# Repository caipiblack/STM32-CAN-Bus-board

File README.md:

STM32-CAN-Bus-board
-------------------

CAN Bus shield with external power supply (12V/24V) for NUCLEO-L432KC board.

All the pins of the NUCLEO-L432KC board are available on the connectors of the shield.

The available pins provide many peripherals (ADC, SPI, I2C, GPIO and more) that can be used for many projects (IOT sensors, security sensors, automation...)

# Hardware

This part describe how the schematic was made, how to mount the PCB and how to test it.

**IMPORTANT: This shield require some modifications on the Nucleo board to works (due to external supply) (see after)**

## Kicad project

The Kicad project as been created with the version 8.0.1 of Kicad.

Most of the symbols and footprints comes from the default libraries.

The custom footprints are stored in the `custom` folder near the Kicad project.

Setup Kicad on Ubuntu 24.04:

```
sudo add-apt-repository ppa:kicad/kicad-8.0-releases
sudo apt update
sudo apt install kicad
```

The last production files are stored in the directory [hardware/rev_a/fab](hardware/rev_a/fab).

## Configuration of the NUCLEO-L432KC board

Some modifications are required to be able to power the Nucleo board from external 3V3 regulator (provided by the shield):
- Remove the jumper!
- Remove SB9.
- Remove SB14.

After these changes:
- The 3V3 power for the STM32 will be provided by "external power source" (the shield).
- The debug/flash side of Nucleo board will not be powered by the "external power source" (the shield).
- To flash or debug the Nucleo board, the Nucleo board must be connected by USB to the computer (The St-Link chip will be powered by 5V>3V regulator in the Nucleo board) AND the 3V3 power must be supplied by the shield (to power the STM32 chip).

## PCB mounting instructions

Mount the components on the board:
1. Take the PCB and fix it to the table.
2. Put solder past on all CMS pads.
3. Configure your hot air machine with something like this:
- Speed: 3/8.
- Temperature: 300°C.
4. Solder the CMS components in this order: D4, D6, D1, D5, D2, U2, U3.
5. Solder the other components in this order: C1, C10, C4, R4, R2, R6, R3, R5, F1, Jumper, C6, C5, L1.
6. Mount the `NUCLEO-L432KC` board in the headers and solder the headers to the PCB (Doing it like this prevent issues with headers that are not perfectly vertical or parallel).
7. Remove the nucleo board from the soldered headers.

## PCB testing instructions

Testing instructions:
- Remove the `NUCLEO-L432KC` board from the headers.
- Power on the board with laboratory power supply configured at 12V with current limited to 50mA.
  - At this point the power consumption (on 12V line) should be less than 10mA.
  - Measure the voltage in the 3V3 pin and check that the voltage is around 3.3V.
- If the previous tests pass, turn off the power and plug the `NUCLEO-L432KC` board in the headers then turn on the power.
  - At this point the power consumption (on 12V line) should be less than 10mA.
- If the previous tests pass, connect the `NUCLEO-L432KC` board to the computer and flash it with the template project.
- Test the CAN interface:
  - Plug a USB<>CAN device from a Linux computer to the board.
  - On the computer, execute these commands:
```
sudo apt-get install can-utils
sudo modprobe vcan
sudo ip link add dev can0 type vcan
sudo ip link set up can0 type can bitrate 250000
candump -td -a can0
```
  - Reset the board
  - On the `candump` you should see something like this:
```
 (000.000000)  can0  71D   [1]  00                        '.'
```

# Software

This repository comes with a demo software in the `software` directory: This software act like a CANopen node and permits to control the LED of the `NUCLEO-L432KC` board.

This guide also describe how to create a project from scratch for the `STM32-CAN-Bus-board` board.

The LED can be controlled by writing in the object at index `0x6001`. (See examples at `CANopenLinux` section).

## Tools setup

1. Download and install `STM32CubeIDE` from [here](https://www.st.com/en/development-tools/stm32cubeide.html)
2. (Optional) Download and install `STM32CubeProg` from [here](https://www.st.com/en/development-tools/stm32cubeprog.html). (This tool can be used to only flash the `NUCLEO-L432KC` board without the IDE)

### Compatibility issues of STM32CubeIDE with Ubuntu 24.04

There are issues with `STM32CubeIDE` on `Ubuntu 24.04` because it has a dependecy to `libncurses5` and this is not available with this version of Ubuntu.

This dependency is required by the `arm-none-eabi-gdb` provided by ST.

To resolve the problem:
- Install the generic linux version of `STM32CubeIDE` instead of the version from `.deb` (as it will not check the dependency).
- Install `arm-none-eabi-gdb` or `gdb-multiarch` and create a link to provide `arm-none-eabi-gdb`:
```
sudo apt install gdb-multiarch
sudo ln -s /usr/bin/gdb-multiarch /usr/bin/arm-none-eabi-gdb
```
- In your project configuration `Project Properties -> C/C++ Build -> Environment -> PATH` add `/usr/bin` at the first place to use `arm-none-eabi-gdb` provided by `/usr/bin` instead of ST directories.

## Create a project from scratch

Base project creation:
1. Open `STM32CubeIDE`.
2. Press `File > New > STM32 Project`.
3. Press `Board Selector`.
4. Search `Commercial Part Number` with `NUCLEO-L432KC`, then select it and press Next
5. Specify the `Project Name` and `Location`, then press `Finish`.
6. Configure the peripheral in defaults state and open the configuration tool (or open `.ioc` file).
7. Change the configuration of `PA0` to `Reset_State` as we don't have MCO clock source when the `NUCLEO-L432KC` is externaly powered from 3V3 (because MCO comes from the St-Link chip and it is not powered in this situation).
8. In `Clock Configuration`:
- Select `System Clock Mux` to use `PLLCLK`
- Select `PLL Source Mux` to `MSI`
- Configure the PLL with `X48` and `/4` to get 48Mhz in SYSCLK and APBs

For the integration of `CANopenNode` stack see the README of [CanOpenSTM32](https://github.com/CANopenNode/CanOpenSTM32):
1. From configuration tool configure the CAN interface:
- Activate `CAN1`
- Activate all the interrupts of `CAN1`
- Enable `Automatic Bus-Off Management`
- Enable `Automatic Wake-Up Mode`
- Enable `Automatic Retransmission`
- Configure the Bit timing parameters, you can use [this generator](http://www.bittiming.can-wiki.info/). The clock for `CAN1` is `APB1` (datasheet). In my case with a clock of 48Mhz and desired bitrate of 250Kbit/s I set:
  - Prescaler: 12
  - Time Quanta in Bit Segment 1: 13 Times
  - Time Quanta in Bit Segment 2: 2 Times
2. From configuration tool configure a timer for `CANopenNode` stack:
- Activate `TIM16`
- Enable the interrupt of `TIM16`
- Configure `TIM16` to get 1ms. Note that `TIM16` use `APB2` clock. In my case with a clock of 48Mhz I set:
  - Prescaler (PSC - 16 bits value): 48-1
  - Counter Period (AutoReload Register - 16 bits value ): 1000-1
3. Clone `CanOpenSTM32` somewhere in your computer [see here](https://github.com/CANopenNode/CanOpenSTM32)
4. Take `CANopenNode` and `CANopenNode_STM32` directories from the cloned repo and copy that in your project (from the IDE)
5. Add `CANopenNode` and `CANopenNode_STM32` to `Source locations` in `Project Properties -> C/C++ General -> Paths and Symbols -> Source Locations`. Then add an exclusion filter for `example/` folder for `CANopenNode` folder
6. Add `CANopenNode` and `CANopenNode_STM32` to `Project Properties -> C/C++ General -> Paths and Symbols -> Includes` under `GNU C` items
7. In your `main.c`, add `#include "CO_app_STM32.h"`:
```
/* Private includes ----------------------------------------------------------*/
/* USER CODE BEGIN Includes */
#include "CO_app_STM32.h"
/* USER CODE END Includes */
```
8. In the `main.c` file, call `canopen_app_interrupt()` when the timer ticks at 1ms:
```
/* USER CODE BEGIN 4 */
void HAL_TIM_PeriodElapsedCallback(TIM_HandleTypeDef *htim) {
	  // Handle CANOpen app interrupts
	  if (htim == canopenNodeSTM32->timerHandle) {
	      canopen_app_interrupt();
	  }
}
/* USER CODE END 4 */
```
9. In the `main.c` file, configure the `CANopenNode` stack and call the `canopen_app_process()` function in the main loop:
```
int main(void)
{
  // ...

  /* Initialize all configured peripherals */
  // ...
  /* USER CODE BEGIN 2 */
  CANopenNodeSTM32 canOpenNodeSTM32;
  canOpenNodeSTM32.CANHandle = &hcan1;
  canOpenNodeSTM32.HWInitFunction = MX_CAN1_Init;
  canOpenNodeSTM32.timerHandle = &htim16;
  canOpenNodeSTM32.desiredNodeID = 20;
  canOpenNodeSTM32.baudrate = 250;
  canopen_app_init(&canOpenNodeSTM32);
  /* USER CODE END 2 */

  /* Infinite loop */
  /* USER CODE BEGIN WHILE */
  while (1)
  {
    /* USER CODE END WHILE */

    /* USER CODE BEGIN 3 */
	  canopen_app_process();
  }
  /* USER CODE END 3 */
}
```
10. Flash the board and execute the CAN tests described in `PCB testing instructions`.

## Configure the object dictionary

1. Find the last release of `CANopenEditor` and download the binaries [link](https://github.com/CANopenNode/CANopenEditor/releases)
2. Extract the release binary archive
3. Open `EDSEditor.exe` with wine:
```
wine net481/EDSEditor.exe
```
4. Open the file `CANopenNode_STM32/DS301_profile.xpd`

## CANopenLinux

CANopenLinux can be used as a gateway to communicate with CANopen devices using socket/stdio commands.

Setup the CAN interface:
```
sudo apt-get install can-utils
sudo modprobe vcan
# Do it only if can0 is not already mounted!
#sudo ip link add dev can0 type vcan
sudo ip link set up can0 type can bitrate 250000
```

Download and install CANopenLinux:
```
git clone https://github.com/CANopenNode/CANopenLinux.git
cd CANopenLinux
git submodule update --init --recursive
make
```

Read an OD entry from the computer:
```
./canopend can0 -i 1 -c "stdio"
20 r 0x1000 0
[0] 34 12 00 00
```

Write an OD entry from the computer:
```
./canopend can0 -i 1 -c "stdio"
20 w 0x6001 0 U32 0
[0] OK
```

_In my example, 0x6001 controls the LED!_

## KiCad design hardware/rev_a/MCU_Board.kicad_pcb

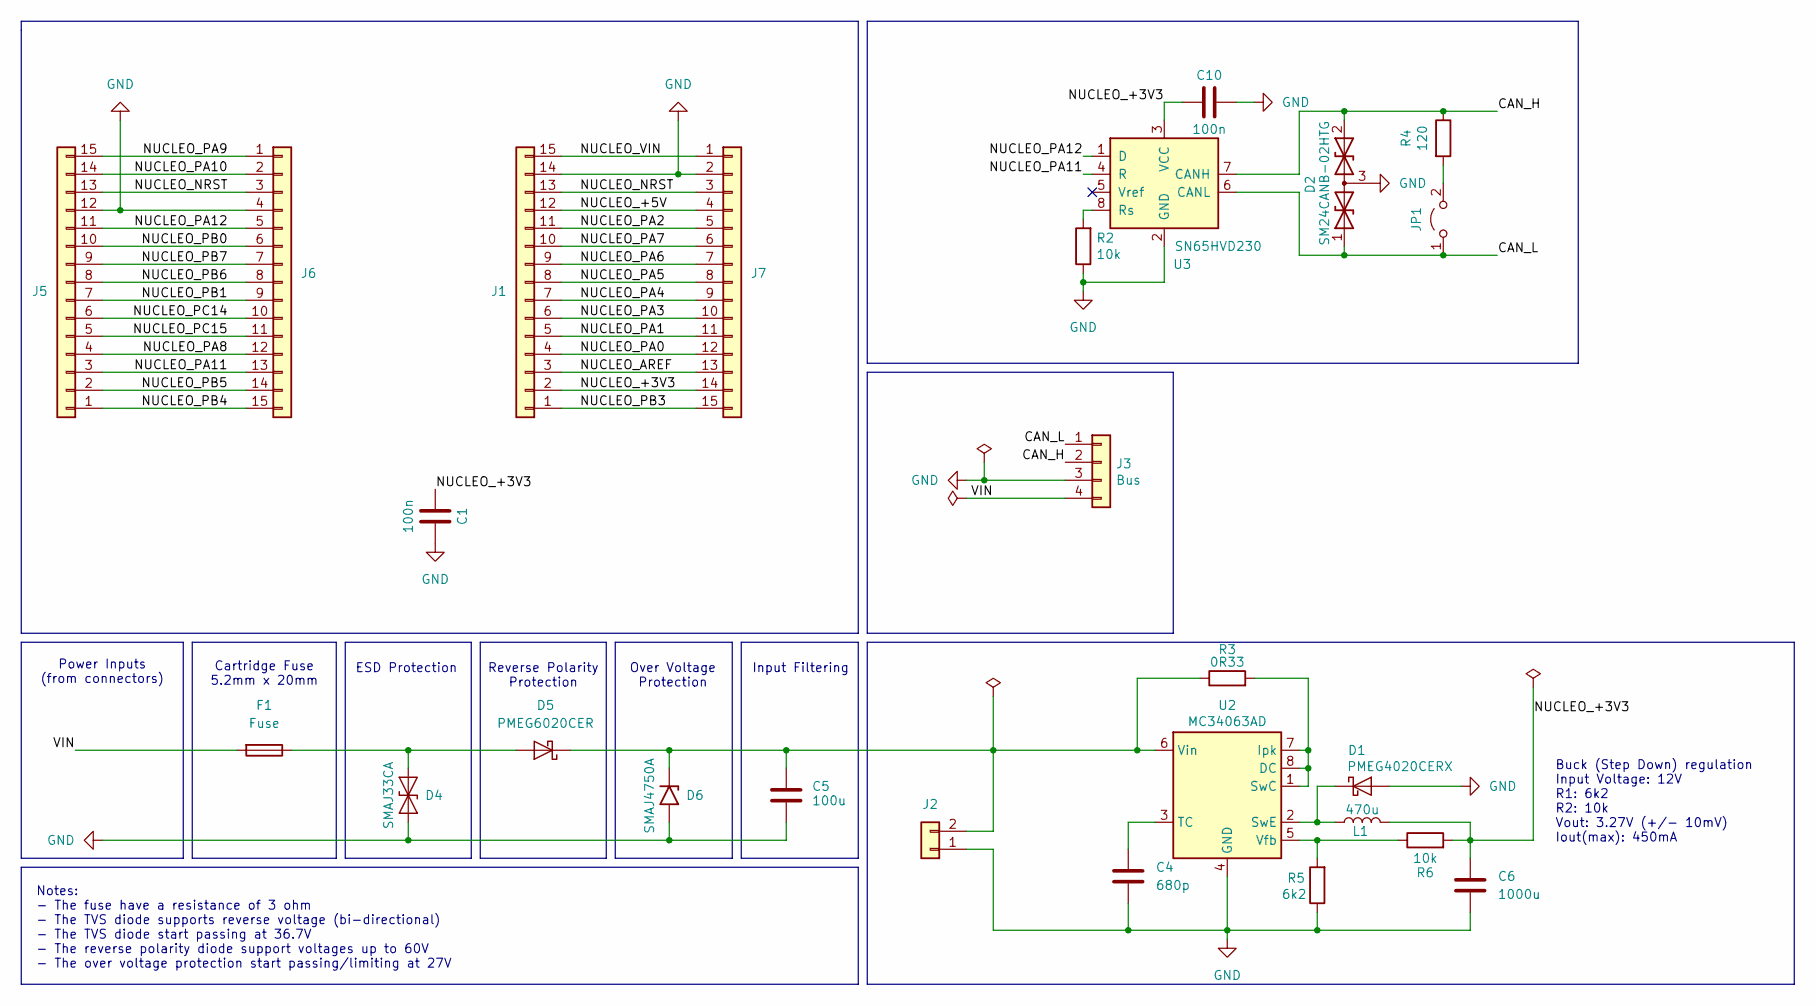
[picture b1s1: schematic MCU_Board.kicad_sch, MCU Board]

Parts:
C1, C10: 100n; C_Disc_D5.0mm_W2.5mm_P5.00mm
C4: 680p; C_Disc_D5.0mm_W2.5mm_P5.00mm
C5: 100u; CP_Radial_D10.0mm_P5.00mm
C6: 1000u; CP_Radial_D10.0mm_P5.00mm
D1: PMEG4020CERX; Nexperia_CFP3_SOD-123W
D2: SM24CANB-02HTG; SOT-23_Handsoldering
D4: SMAJ33CA; D_SMA
D5: PMEG6020CER; Nexperia_CFP3_SOD-123W
D6: SMAJ4750A; D_SMA
F1: Fuse; Fuseholder_Clip-5x20mm_Littelfuse_100_Inline_P20.50x4.60mm_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
J1, J5, J6, J7: Conn_01x15; PinHeader_1x15_P2.54mm_Vertical
J2: Conn_01x02; PinHeader_1x02_P2.54mm_Vertical
J3: Bus; PhoenixContact_MSTBVA_2,5_4-G-5,08_1x04_P5.08mm_Vertical_cu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
JP1: Jumper_2_Open; PinHeader_1x02_P2.54mm_Vertical
L1: 470u; L_Radial_D8.7mm_P5.00mm_Fastron_07HCP
R2, R6: 10k; R_Axial_DIN0309_L9.0mm_D3.2mm_P2.54mm_Vertical
R3: 0R33; R_Axial_DIN0309_L9.0mm_D3.2mm_P2.54mm_Vertical
R4: 120; R_Axial_DIN0309_L9.0mm_D3.2mm_P2.54mm_Vertical
R5: 6k2; R_Axial_DIN0309_L9.0mm_D3.2mm_P2.54mm_Vertical
U2: MC34063AD; SOIC-8_3.9x4.9mm_P1.27mm
U3: SN65HVD230; SOIC-8_3.9x4.9mm_P1.27mm

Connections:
/CAN_H: D2.2 (A2), J3.2, R4.1, U3.7 (CANH)
/CAN_L: D2.1 (A1), J3.1, JP1.1 (A), U3.6 (CANL)
/NUCLEO_+3V3: C1.2, C6.1, C10.2, J1.2, J7.14, L1.2, R6.2, U3.3 (VCC)
/NUCLEO_+5V: J1.12, J7.4
/NUCLEO_AREF: J1.3, J7.13
/NUCLEO_NRST: J1.13, J5.13, J6.3, J7.3
/NUCLEO_PA0: J1.4, J7.12
/NUCLEO_PA1: J1.5, J7.11
/NUCLEO_PA2: J1.11, J7.5
/NUCLEO_PA3: J1.6, J7.10
/NUCLEO_PA4: J1.7, J7.9
/NUCLEO_PA5: J1.8, J7.8
/NUCLEO_PA6: J1.9, J7.7
/NUCLEO_PA7: J1.10, J7.6
/NUCLEO_PA8: J5.4, J6.12
/NUCLEO_PA9: J5.15, J6.1
/NUCLEO_PA10: J5.14, J6.2
/NUCLEO_PA11: J5.3, J6.13, U3.4 (R)
/NUCLEO_PA12: J5.11, J6.5, U3.1 (D)
/NUCLEO_PB0: J5.10, J6.6
/NUCLEO_PB1: J5.7, J6.9
/NUCLEO_PB3: J1.1, J7.15
/NUCLEO_PB4: J5.1, J6.15
/NUCLEO_PB5: J5.2, J6.14
/NUCLEO_PB6: J5.8, J6.8
/NUCLEO_PB7: J5.9, J6.7
/NUCLEO_PC14: J5.6, J6.10
/NUCLEO_PC15: J5.5, J6.11
/NUCLEO_VIN: J1.15, J7.1
/VIN: F1.2, J3.4
GND: C1.1, C4.2, C5.2, C6.2, C10.1, D1.2 (A), D2.3 (common), D4.1 (A1), D6.2 (A2), J1.14, J2.1, J3.3, J5.12, J6.4, J7.2, R2.1, R5.1, U2.4 (GND), U3.2 (GND)
unnamed: D1.1 (K), L1.1, U2.2 (SwE)
unnamed: D4.2 (A2), D5.2 (A), F1.1
unnamed: C5.1, D5.1 (K), D6.1 (A1), J2.2, R3.1, U2.6 (Vin)
unnamed: JP1.2 (B), R4.2
unnamed: R3.2, U2.1 (SwC), U2.7 (Ipk), U2.8 (DC)
unnamed: C4.1, U2.3 (TC)
unnamed: R5.2, R6.1, U2.5 (Vfb)
unnamed: R2.2, U3.8 (Rs)

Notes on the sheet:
Reverse Polarity Protection
Over Voltage Protection
ESD Protection
Input Filtering
Cartridge Fuse 5.2mm x 20mm
Notes: - The fuse have a resistance of 3 ohm - The TVS diode supports reverse voltage (bi-directional) - The TVS diode start passing at 36.7V - The reverse polarity diode support voltages up to 60V - The over voltage protection start passing/limiting at 27V
Power Inputs (from connectors)
Buck (Step Down) regulation Input Voltage: 12V R1: 6k2 R2: 10k Vout: 3.27V (+/- 10mV) Iout(max): 450mA

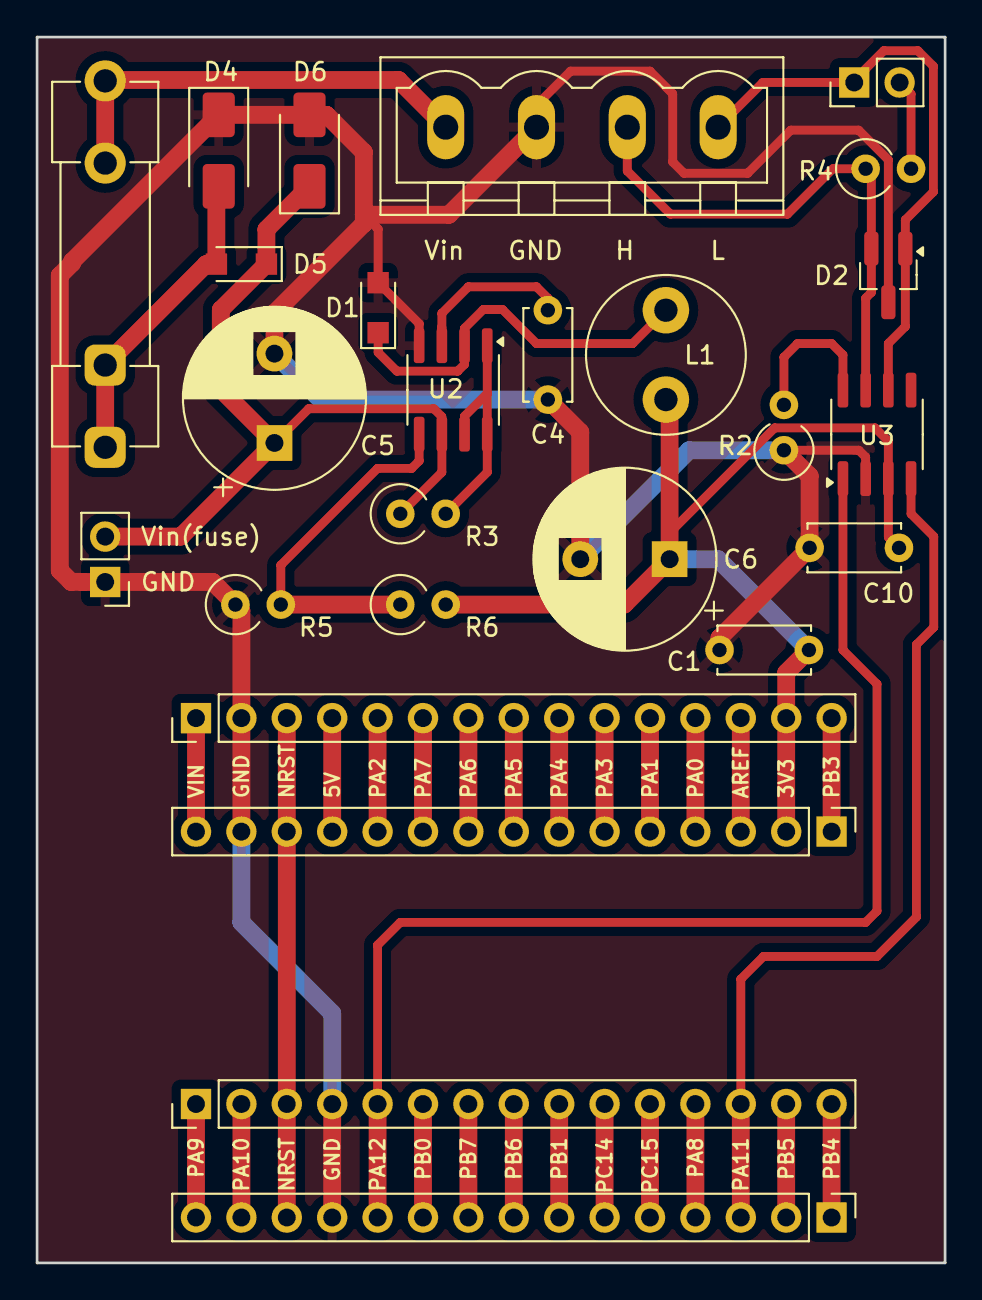
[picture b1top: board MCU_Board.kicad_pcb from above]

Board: 2 copper layers, 50.8 x 68.6 mm, 26 parts (0 on the bottom side), 39 nets.

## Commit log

2023-07-30 Update PCB and center the board and check connectors alignment
2023-08-01 Fix all the warnings or errors and add the 'fab' folder with all the required files for production.
2023-08-02 Add a changelog and refactor the PCB (the labels of the main connector are centered)
2023-08-02 Remove the dependancy with external libraries, the TVS diode is now using the default symbol and a custom footprint
2023-08-10 Update the reference of the input connector
2023-08-10 Update the reference of various components
2024-04-21 Refactorisation de l'étage d'entrée en utilisant un régulateur à découpage DC/DC type buck
2024-04-21 Update the README and docs
2024-04-21 Version under review by PCBWay
2024-05-01 Fix resistor value around DC/DC converter
2024-05-03 Update the PDF rev A
2024-05-04 Version under review by PCBWay (Nucleo Shield)
2024-05-18 Remove datasheets/guides
2024-05-18 Update the README with PCB mounting instructions
2024-05-18 Update the README
2024-05-19 Update the TemplateProject
2024-05-19 Update the template project: Add a TPDO and make possible to control the LED using SDO
2024-05-26 Update the CHANGELOG of hardware
2024-05-26 1 kicad project creation (#2)
    Add the hardware project (+ build/test instructions) and a template software project.
2024-06-01 Add an example of CANopen sensor
2024-06-01 Update the sensor example
